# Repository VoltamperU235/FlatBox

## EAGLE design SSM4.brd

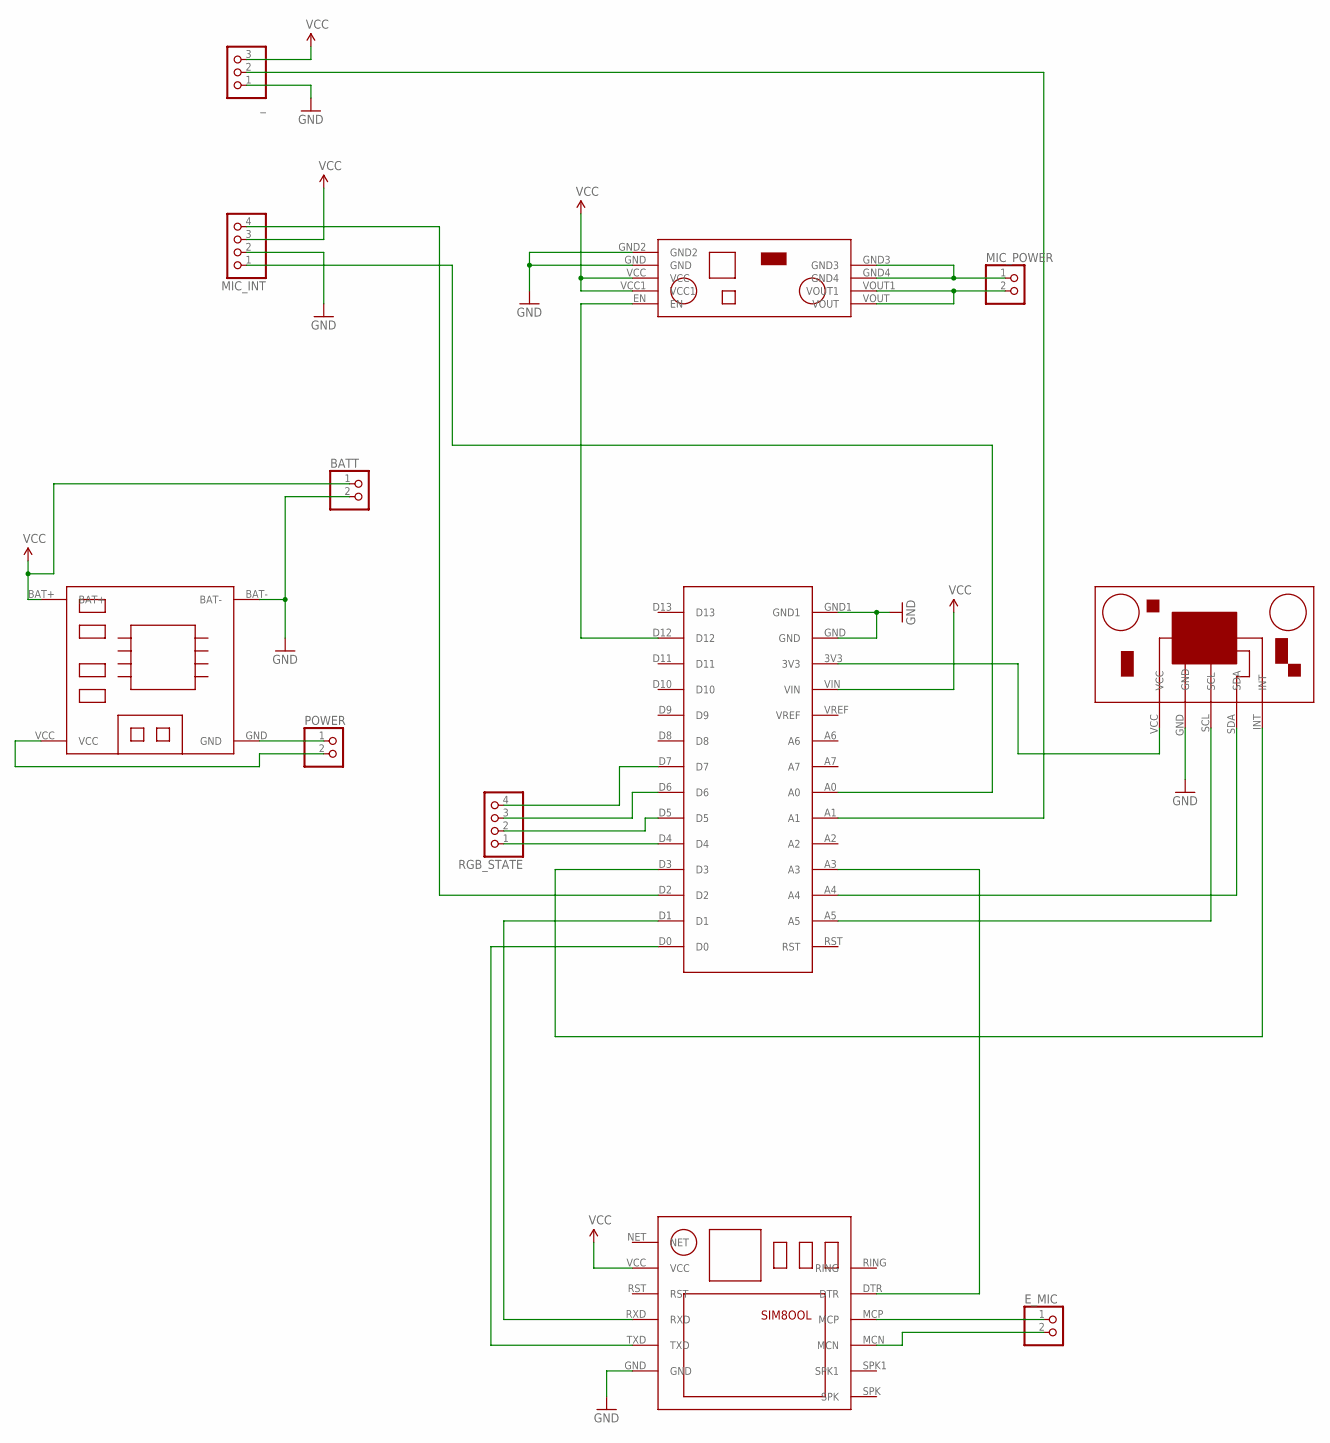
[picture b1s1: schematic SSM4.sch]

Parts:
BATT: PINHD-1X2; 1X02
E_MIC: PINHD-1X2; 1X02
MIC_INT: PINHD-1X4; 1X04
MIC_POWER: PINHD-1X2; 1X02
POWER: PINHD-1X2; 1X02
RGB_STATE: PINHD-1X4; 1X04
U$1: ACELEROMETER
U$2: POLOLU_STEP_UP_DOWN
U$3: CHARGER
U$4: SIM8OOL
U$5: ULTRA_MINI
_: PINHD-1X3; 1X03

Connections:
GND: BATT.2, MIC_INT.2, U$1.GND, U$2.GND, U$2.GND2, U$3.BAT-, U$4.GND, U$5.GND, U$5.GND1, _.1
unnamed: U$2.EN, U$5.D12
unnamed: U$4.TXD, U$5.D0
unnamed: U$4.RXD, U$5.D1
unnamed: U$1.VCC, U$5.3V3
unnamed: U$4.DTR, U$5.A3
unnamed: U$1.INT, U$5.D3
unnamed: U$1.SCL, U$5.A5
unnamed: U$1.SDA, U$5.A4
unnamed: E_MIC.1, U$4.MCP
unnamed: E_MIC.2, U$4.MCN
unnamed: POWER.1, U$3.GND
unnamed: POWER.2, U$3.VCC
unnamed: MIC_POWER.1, U$2.GND3, U$2.GND4
unnamed: MIC_POWER.2, U$2.VOUT, U$2.VOUT1
unnamed: MIC_INT.1, U$5.A0
unnamed: MIC_INT.4, U$5.D2
unnamed: U$5.A1, _.2
unnamed: RGB_STATE.1, U$5.D4
unnamed: RGB_STATE.2, U$5.D5
unnamed: RGB_STATE.3, U$5.D6
unnamed: RGB_STATE.4, U$5.D7
VCC: BATT.1, MIC_INT.3, U$2.VCC, U$2.VCC1, U$3.BAT+, U$4.VCC, U$5.VIN, _.3

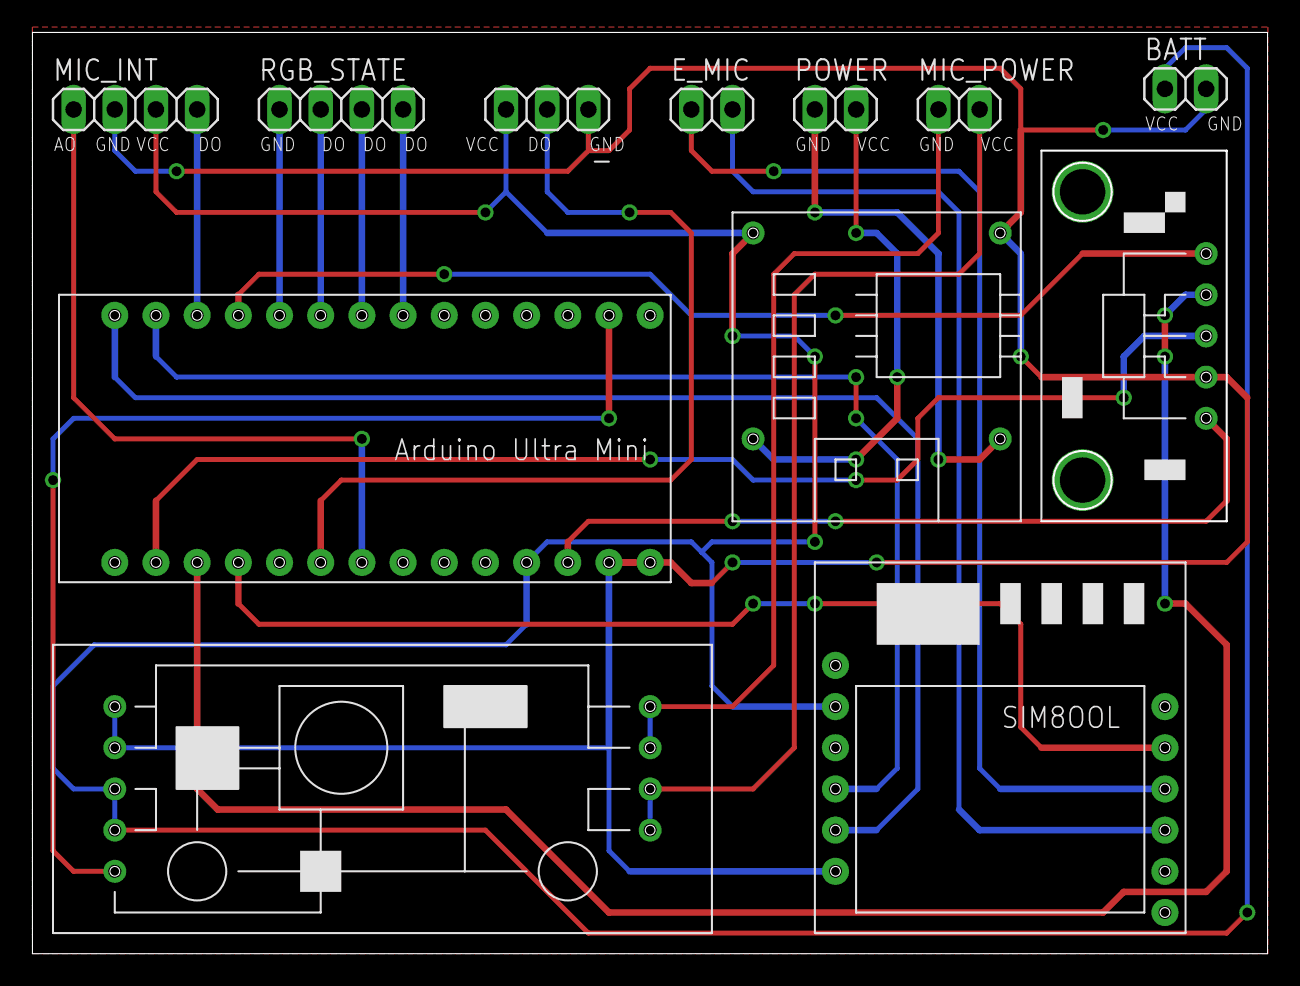
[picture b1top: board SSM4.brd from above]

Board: 2 copper layers, 76.1 x 56.7 mm, 12 parts (0 on the bottom side), 23 nets.

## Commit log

2018-09-05 mi primer commit
2018-09-27 Add files via upload
    Fase final del examen de Tecnico en Electronica Industrial. INTECAP 2018

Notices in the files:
parts and their libraries:
SparkFun-Aesthetics: Licensing: Creative Commons ShareAlike 4.0 International - https://creativecommons.org/licenses/by-sa/4.0
